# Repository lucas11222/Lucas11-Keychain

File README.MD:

# Lucas 11 Keychain.

## What is it?
Is my personal keychain for my keys for my house.
Also i added an extra that if you put a battery in the cell the leds show up and it seems like a smilly face.

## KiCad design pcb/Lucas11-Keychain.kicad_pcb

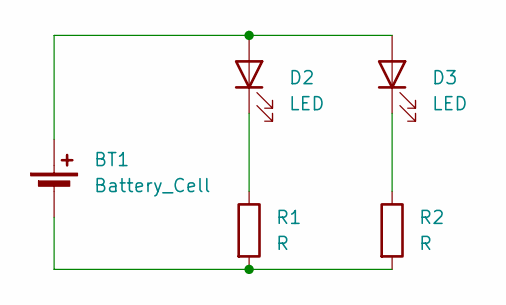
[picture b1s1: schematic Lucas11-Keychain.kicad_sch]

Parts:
BT1: Battery_Cell
D2, D3: LED
R1, R2: R

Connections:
unnamed: BT1.1 (+), D2.2 (A), D3.2 (A)
unnamed: BT1.2 (-), R1.2, R2.2
unnamed: D2.1 (K), R1.1
unnamed: D3.1 (K), R2.1

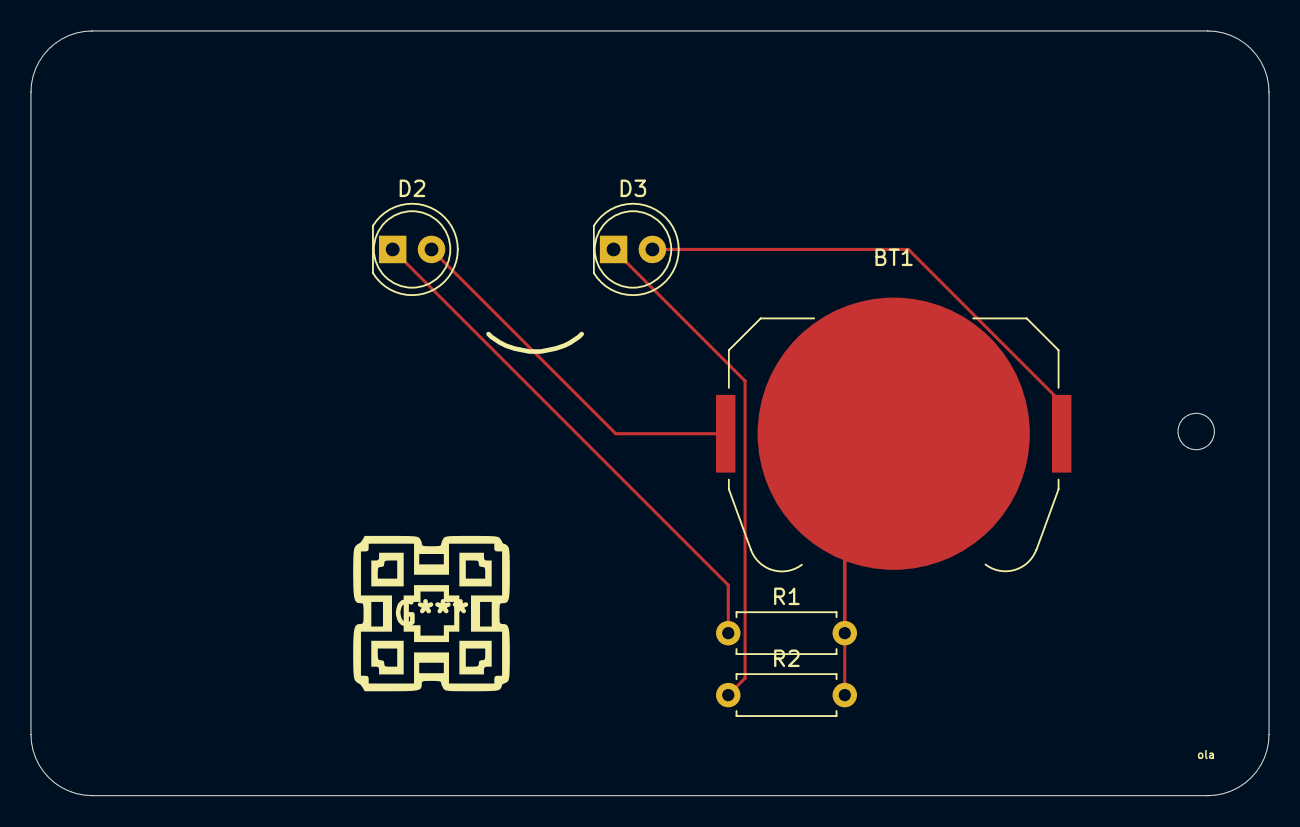
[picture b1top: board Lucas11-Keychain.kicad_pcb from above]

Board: 2 copper layers, 81.0 x 50.0 mm, 5 parts (0 on the bottom side), 4 nets.
